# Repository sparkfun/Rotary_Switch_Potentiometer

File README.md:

Rotary Switch Potentiometer
========================================

Breakout board for 10-position rotary switch that allows you to add resistors to configure it as a custom stepped potentiometer.

[
*Rotary Switch Potentiometer (BOB-13099)*](https://www.sparkfun.com/products/13099)

The Rotary Switch Potentiometer is a board that allows you to add some resistors to our one of our 10-position rotary switches, turning it into a potentiometer with ten discrete steps.  [The hookup guide can be found here.](https://learn.sparkfun.com/tutorials/rotary-switch-potentiometer-hookup-guide)

More information can be found on the Wiki for this repo. 

This part was created in Eagle v7.1.0, and the demonstration Arduino sketch was written in  Arduino v1.6.1. 

Repository Contents
-------------------
* **/Firmware** - An Arduino sketch to interface with the board. 
* **/Hardware** - All Eagle design files (.brd, .sch, .STL)
* **/Theory** - Spreadsheet to calculate resistor values

Product Versions
----------------
* [BOB-13099](https://www.sparkfun.com/products/13099)- Breakout board itself.

Related Products
----------------

To make the best use of BOB-13099, you'll need some additional components.

* A [10 position Rotary Switch](https://www.sparkfun.com/products/13253).
* Some [resistors](https://www.sparkfun.com/products/10969).
* A [control](https://www.sparkfun.com/products/9998) or [chickenhead](https://www.sparkfun.com/products/9998) knob.
* [Straight](https://www.sparkfun.com/products/116) or [right-angle](https://www.sparkfun.com/products/553) snappable headers.

Version History
---------------
* [vExxFxxZxxHxxLxxSxx](URL for tag specific to this version) description 
* [vEyyFyyZyyHyyLyySyy](URL for tag specific to this version) description

License Information
-------------------
The hardware is released under [Creative Commons ShareAlike 4.0 International](https://creativecommons.org/licenses/by-sa/4.0/).
The code is beerware; if you see me (or any other SparkFun employee) at the local, and you've found our code helpful, please buy us a round!

Distributed as-is; no warranty is given.

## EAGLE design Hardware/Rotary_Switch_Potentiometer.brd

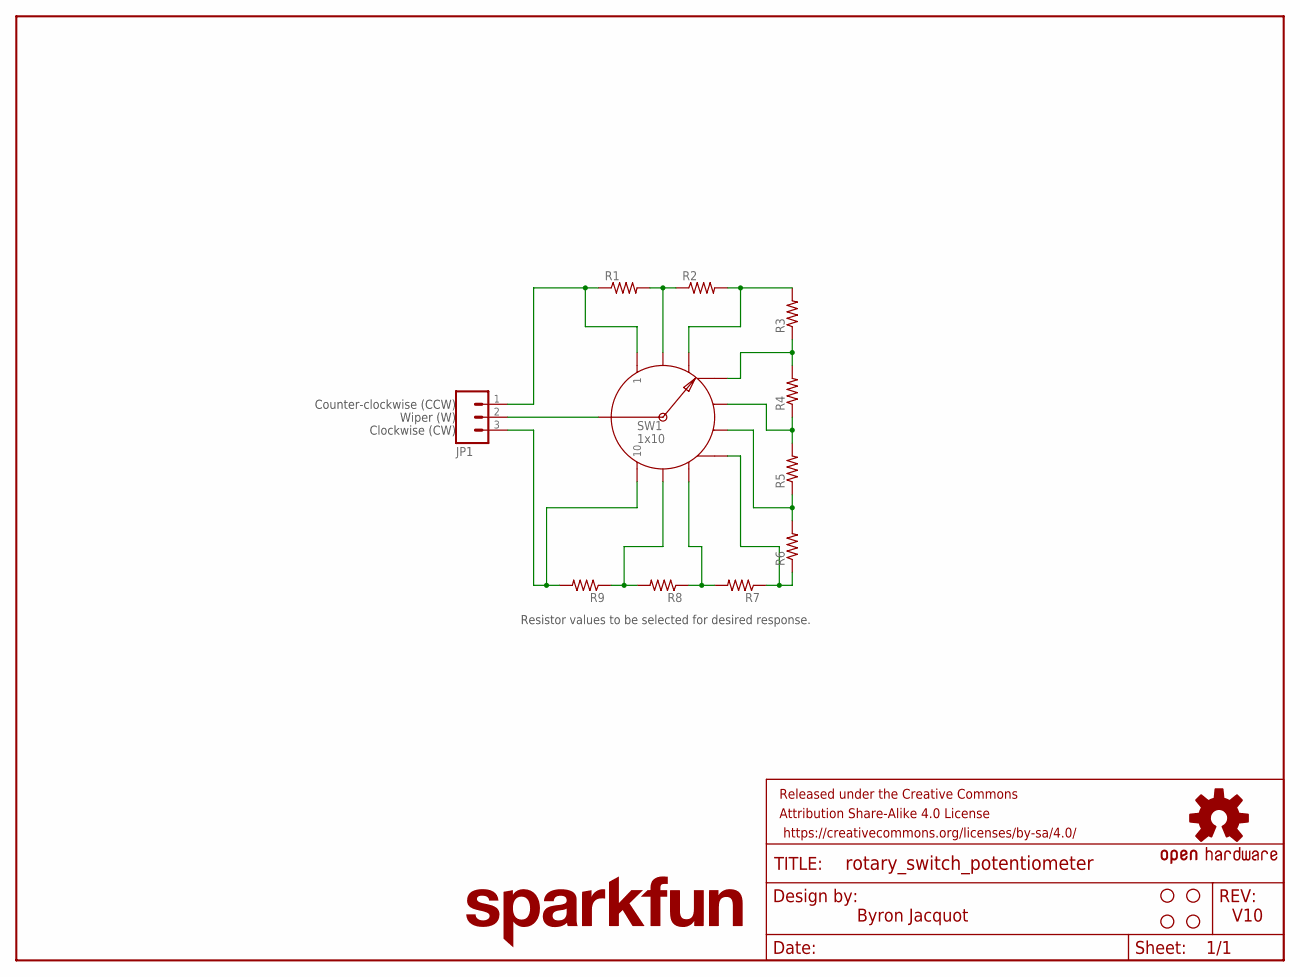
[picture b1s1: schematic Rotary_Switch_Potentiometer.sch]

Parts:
FRAME1: FRAME-LETTER; CREATIVE_COMMONS
JP1: M031X03_NO_SILK; 1X03_NO_SILK
LOGO1: OSHW-LOGOM; OSHW-LOGO-M
LOGO3: SFE_LOGO_NAME.1_INCH; SFE_LOGO_NAME_.1
R1, R2, R3, R4, R5, R6, R7, R8, R9: RESISTORPTH-1/4W-VERT-KIT; AXIAL-0.1EZ
STANDOFF1, STANDOFF2, STANDOFF5, STANDOFF6: STAND-OFF
SW1: 1x10; ROTARY_SWITCH_1X10_KIT

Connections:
unnamed: JP1.2, SW1.COMMON
unnamed: JP1.1, R1.P$1 (1), SW1.1
unnamed: JP1.3, R9.P$2 (2), SW1.10
unnamed: R7.P$2 (2), R8.P$1 (1), SW1.8
unnamed: R1.P$2 (2), R2.P$1 (1), SW1.2
unnamed: R2.P$2 (2), R3.P$2 (2), SW1.3
unnamed: R3.P$1 (1), R4.P$2 (2), SW1.4
unnamed: R4.P$1 (1), R5.P$2 (2), SW1.5
unnamed: R5.P$1 (1), R6.P$2 (2), SW1.6
unnamed: R6.P$1 (1), R7.P$1 (1), SW1.7
unnamed: R8.P$2 (2), R9.P$1 (1), SW1.9

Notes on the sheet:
Byron Jacquot
V10
Resistor values to be selected for desired response.
Wiper (W)
Counter-clockwise (CCW)
Clockwise (CW)

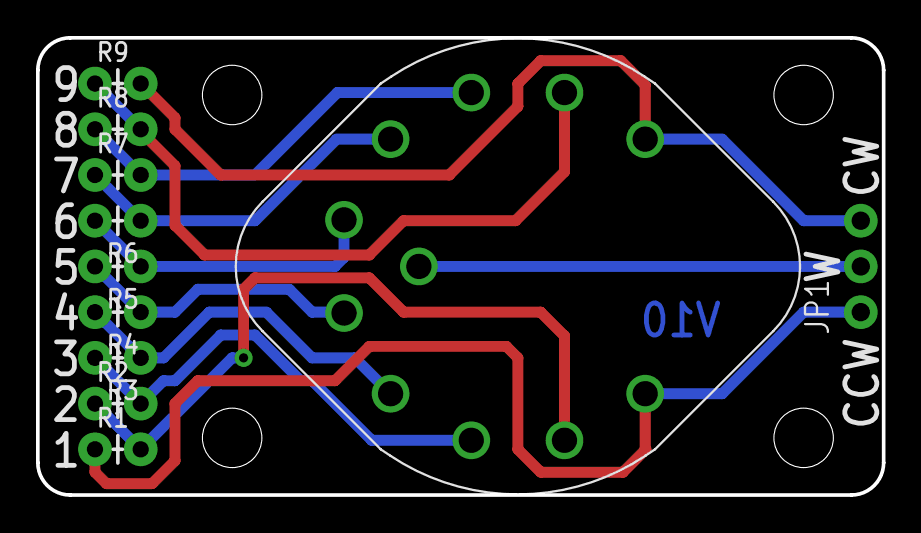
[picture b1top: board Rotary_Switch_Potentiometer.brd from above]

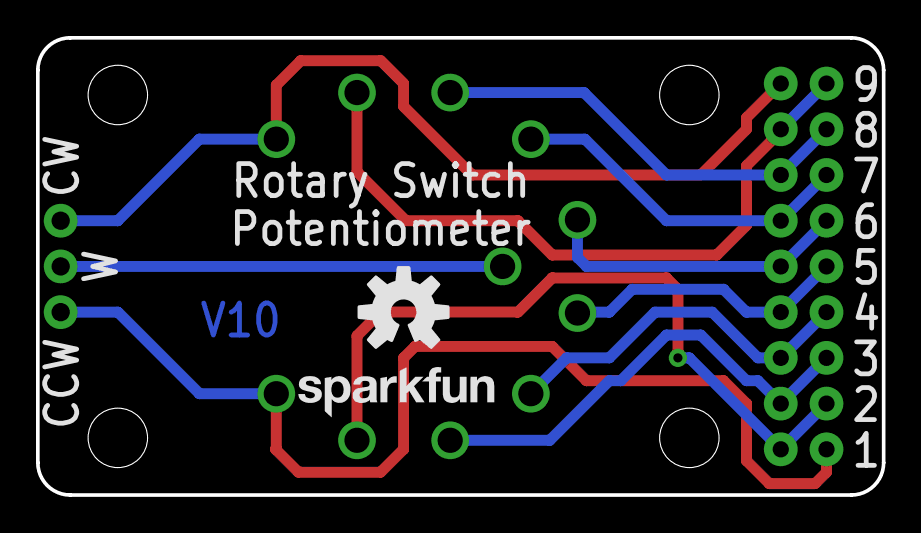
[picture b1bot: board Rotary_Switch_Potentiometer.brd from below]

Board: 2 copper layers, 47.0 x 25.4 mm, 18 parts (2 on the bottom side), 11 nets.

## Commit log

2014-09-02 Initial Commit
    Boilerplate and board files.
2014-09-02 Small schem update.
2014-09-03 Adding spreadsheet for divider calculations
2015-02-21 Updates from working with protos.
    Now has 4 mounting holes.
2015-02-23 Tweaks after engineering group review.
2015-04-29 Updating documentation
    Improved spreadsheet, added Arduino sketch.
2015-04-30 Updating Readme
    Filling in links and such.
2015-04-30 Fixing a few cell arguments in pot-values

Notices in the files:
parts and their libraries:
SparkFun-Aesthetics: Licensing: Creative Commons ShareAlike 4.0 International - https://creativecommons.org/licenses/by-sa/4.0
SparkFun-Aesthetics: Released under the Creative Commons Attribution Share-Alike 4.0 License
SparkFun-Aesthetics: Released under the Creative Commons
